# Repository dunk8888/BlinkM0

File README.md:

# BlinkM0

This is research for a potential new BlinkM, based on ATSAMD21.

It builds on research in previous repos like:

- blinkm_mk2
- samd11toy
- blinkm
- blink1

Some of the proposed features:
- Tiny form, for small embedded uses
- Trinket M0 compatible
- CircuitPython capable
- USB MSD programmable (MSD bootlaoder)
- At least 2 inputs
- logic level-shifters for LEDs

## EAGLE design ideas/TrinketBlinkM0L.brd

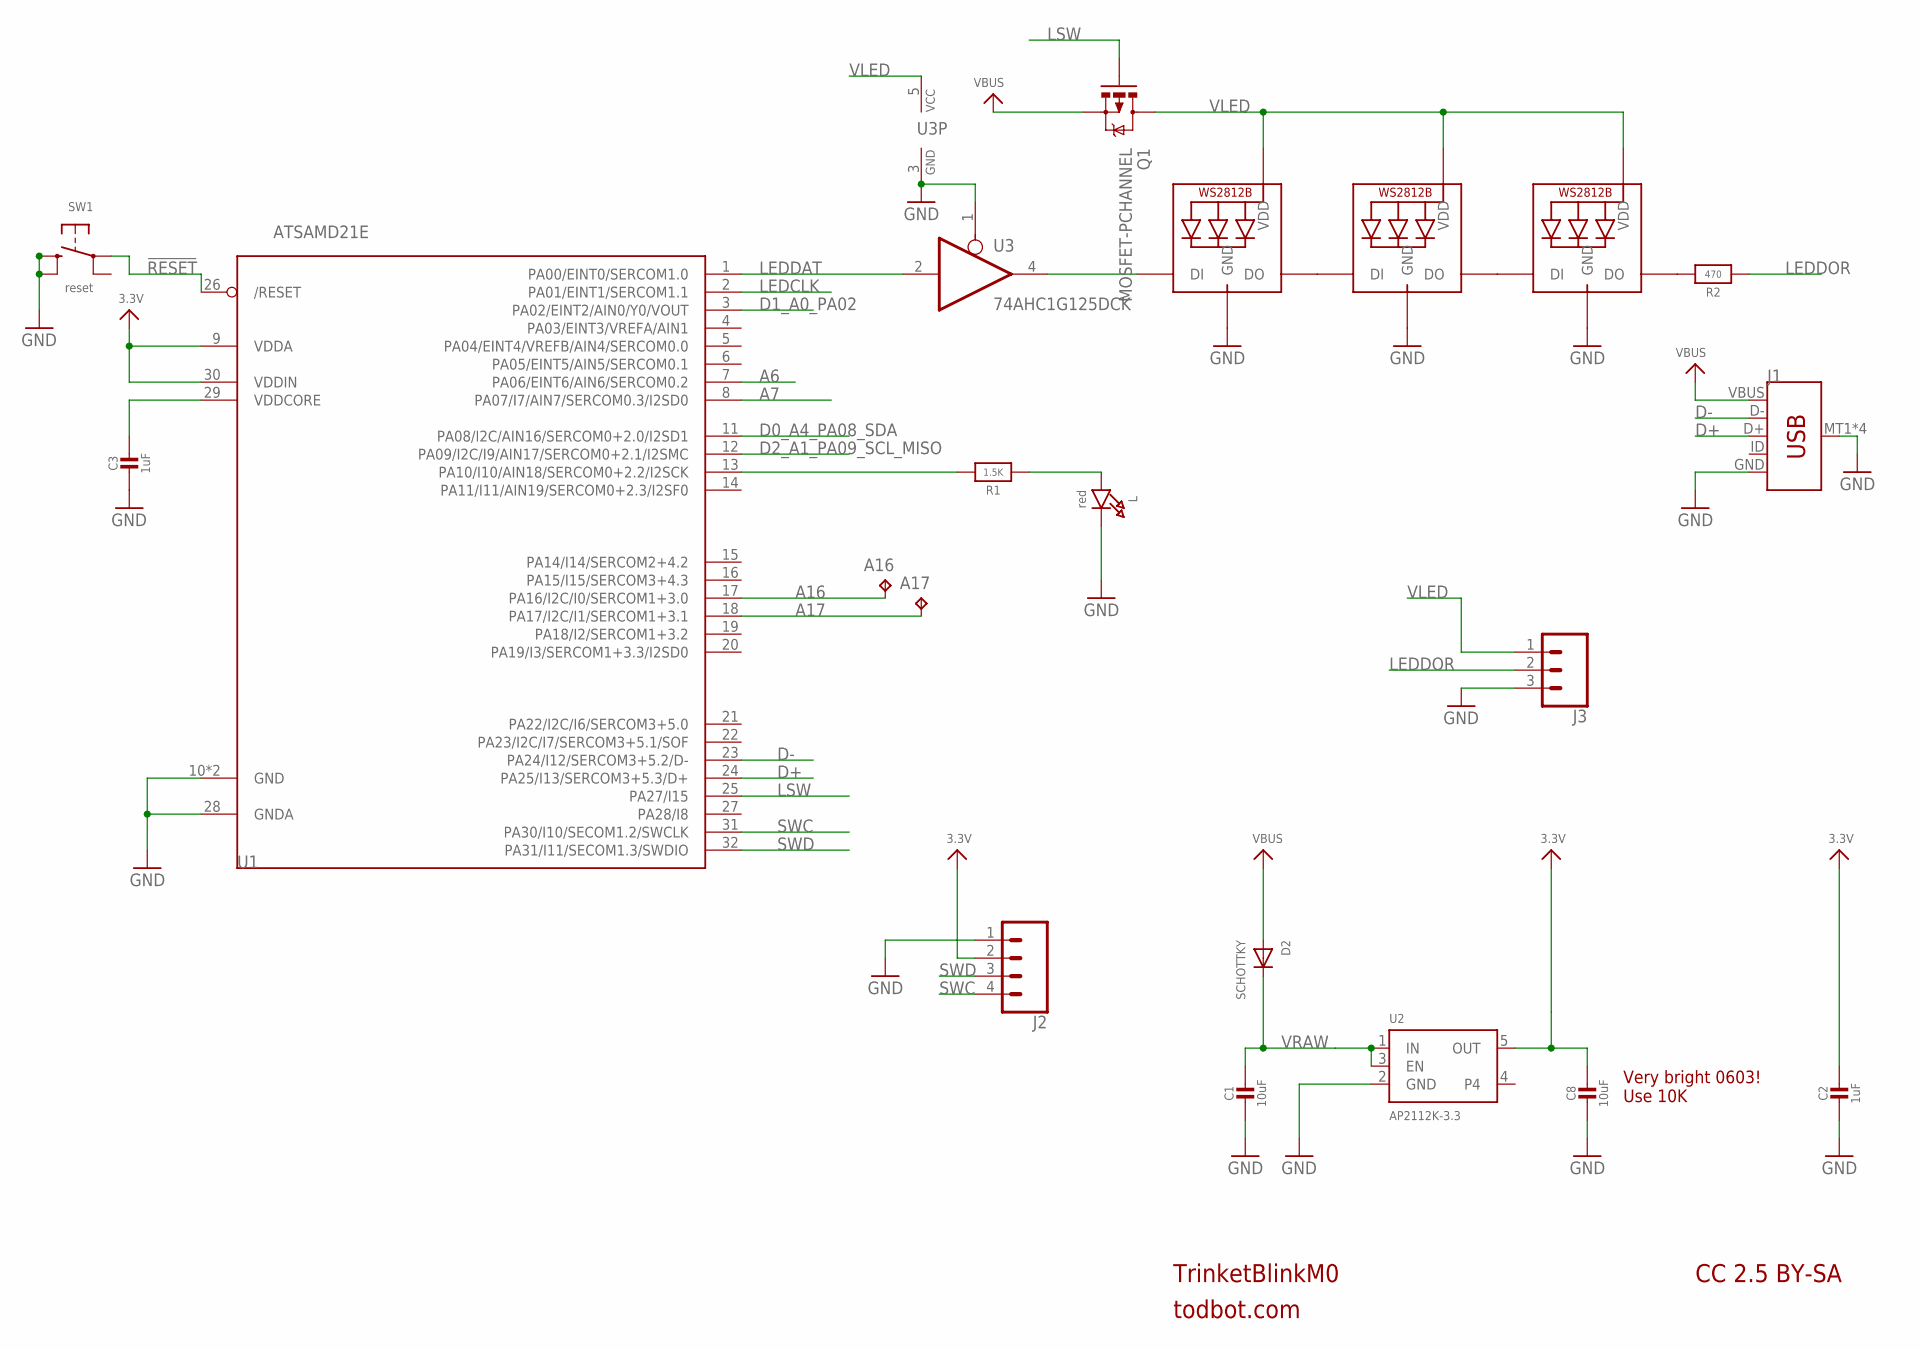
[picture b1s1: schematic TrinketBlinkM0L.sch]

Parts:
A16, A17: TPB1,27; B1,27
C1, C8: 10uF; 0805-NO
C2, C3: 1uF; 0603-NO
D2: SCHOTTKY; SOD-123FL
J1: USB_MICRO-B_SMT; USB-MICROB
J2: CONN_04; 1X04
J3: CONN_03; 1X03
L: red; CHIPLED_0603_NOOUTLINE
LED1, LED2, LED3: WS2812B3535; LED3535
Q1: MOSFET-PCHANNEL; SOT23-3
R1: 1.5K; 0603-NO
R2: 470; 0603-NO
SW1: reset; BTN_KMR2_4.6X2.8
U1: ATSAMD21E; QFN32_5MM
U2: AP2112K-3.3; SOT23-5
U3: 74AHC1G125DCK; SC70-5

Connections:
3.3V: C2.1, C8.1, J2.2, U1.9 (VDDA), U1.30 (VDDIN), U2.5 (OUT)
!RESET: SW1.A, U1.26 (/RESET)
A6: U1.7 (PA06/EINT6/AIN6/SERCOM0.2)
A7: U1.8 (PA07/I7/AIN7/SERCOM0.3/I2SD0)
A16: A16.TP, U1.17 (PA16/I2C/I0/SERCOM1+3.0)
A17: A17.TP, U1.18 (PA17/I2C/I1/SERCOM1+3.1)
D0_A4_PA08_SDA: U1.11 (PA08/I2C/AIN16/SERCOM0+2.0/I2SD1)
D1_A0_PA02: U1.3 (PA02/EINT2/AIN0/Y0/VOUT)
D2_A1_PA09_SCL_MISO: U1.12 (PA09/I2C/I9/AIN17/SERCOM0+2.1/I2SMC)
D+: J1.D+, U1.24 (PA25/I13/SERCOM3+5.3/D+)
D-: J1.D-, U1.23 (PA24/I12/SERCOM3+5.2/D-)
GND: C1.2, C2.2, C3.2, C8.2, J1.GND, J1.MT1 (SHIELD), J1.MT2 (SHIELD), J1.P$1 (SHIELD), J1.P$2 (SHIELD), J2.1, J3.3, L.C, LED1.4 (GND), LED2.4 (GND), LED3.4 (GND), SW1.B (S), SW1.B' (S1), U1.10 (GND), U1.28 (GNDA), U1.33 (GND), U2.2 (GND), U3.1 (OE), U3.3 (GND)
LEDCLK: U1.2 (PA01/EINT1/SERCOM1.1)
LEDDAT: U1.1 (PA00/EINT0/SERCOM1.0), U3.2 (I)
LEDDATO: LED1.1 (DI), U3.4 (O)
LEDDOR: J3.2, R2.1
LSW: Q1.1 (G), U1.25 (PA27/I15)
unnamed: L.A, R1.1
unnamed: R1.2, U1.13 (PA10/I10/AIN18/SERCOM0+2.2/I2SCK)
unnamed: LED1.3 (DO), LED2.1 (DI)
unnamed: LED2.3 (DO), LED3.1 (DI)
unnamed: LED3.3 (DO), R2.2
SWC: J2.4, U1.31 (PA30/I10/SECOM1.2/SWCLK)
SWD: J2.3, U1.32 (PA31/I11/SECOM1.3/SWDIO)
VBUS: D2.A, J1.VBUS, Q1.2 (S)
VDDCORE: C3.1, U1.29 (VDDCORE)
VLED: J3.1, LED1.2 (VDD), LED2.2 (VDD), LED3.2 (VDD), Q1.3 (D), U3.5 (VCC)
VRAW: C1.1, D2.C, U2.1 (IN), U2.3 (EN)

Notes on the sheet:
TrinketBlinkM0
todbot.com
CC 2.5 BY-SA
Very bright 0603! Use 10K

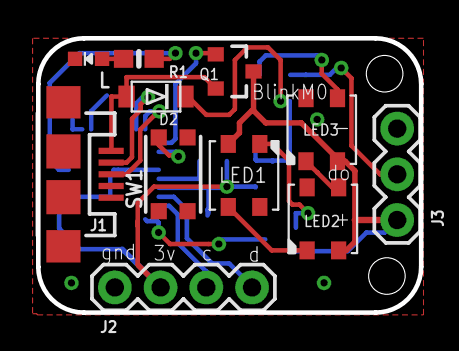
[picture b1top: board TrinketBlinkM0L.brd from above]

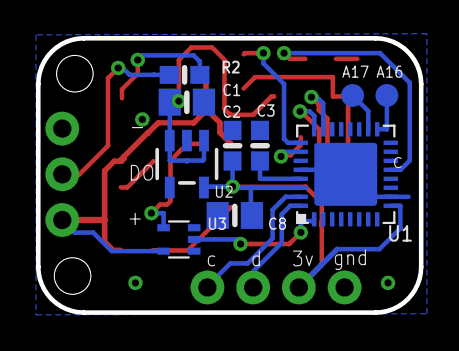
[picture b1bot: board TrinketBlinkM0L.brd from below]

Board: 2 copper layers, 21.3 x 15.2 mm, 21 parts (10 on the bottom side), 22 nets.

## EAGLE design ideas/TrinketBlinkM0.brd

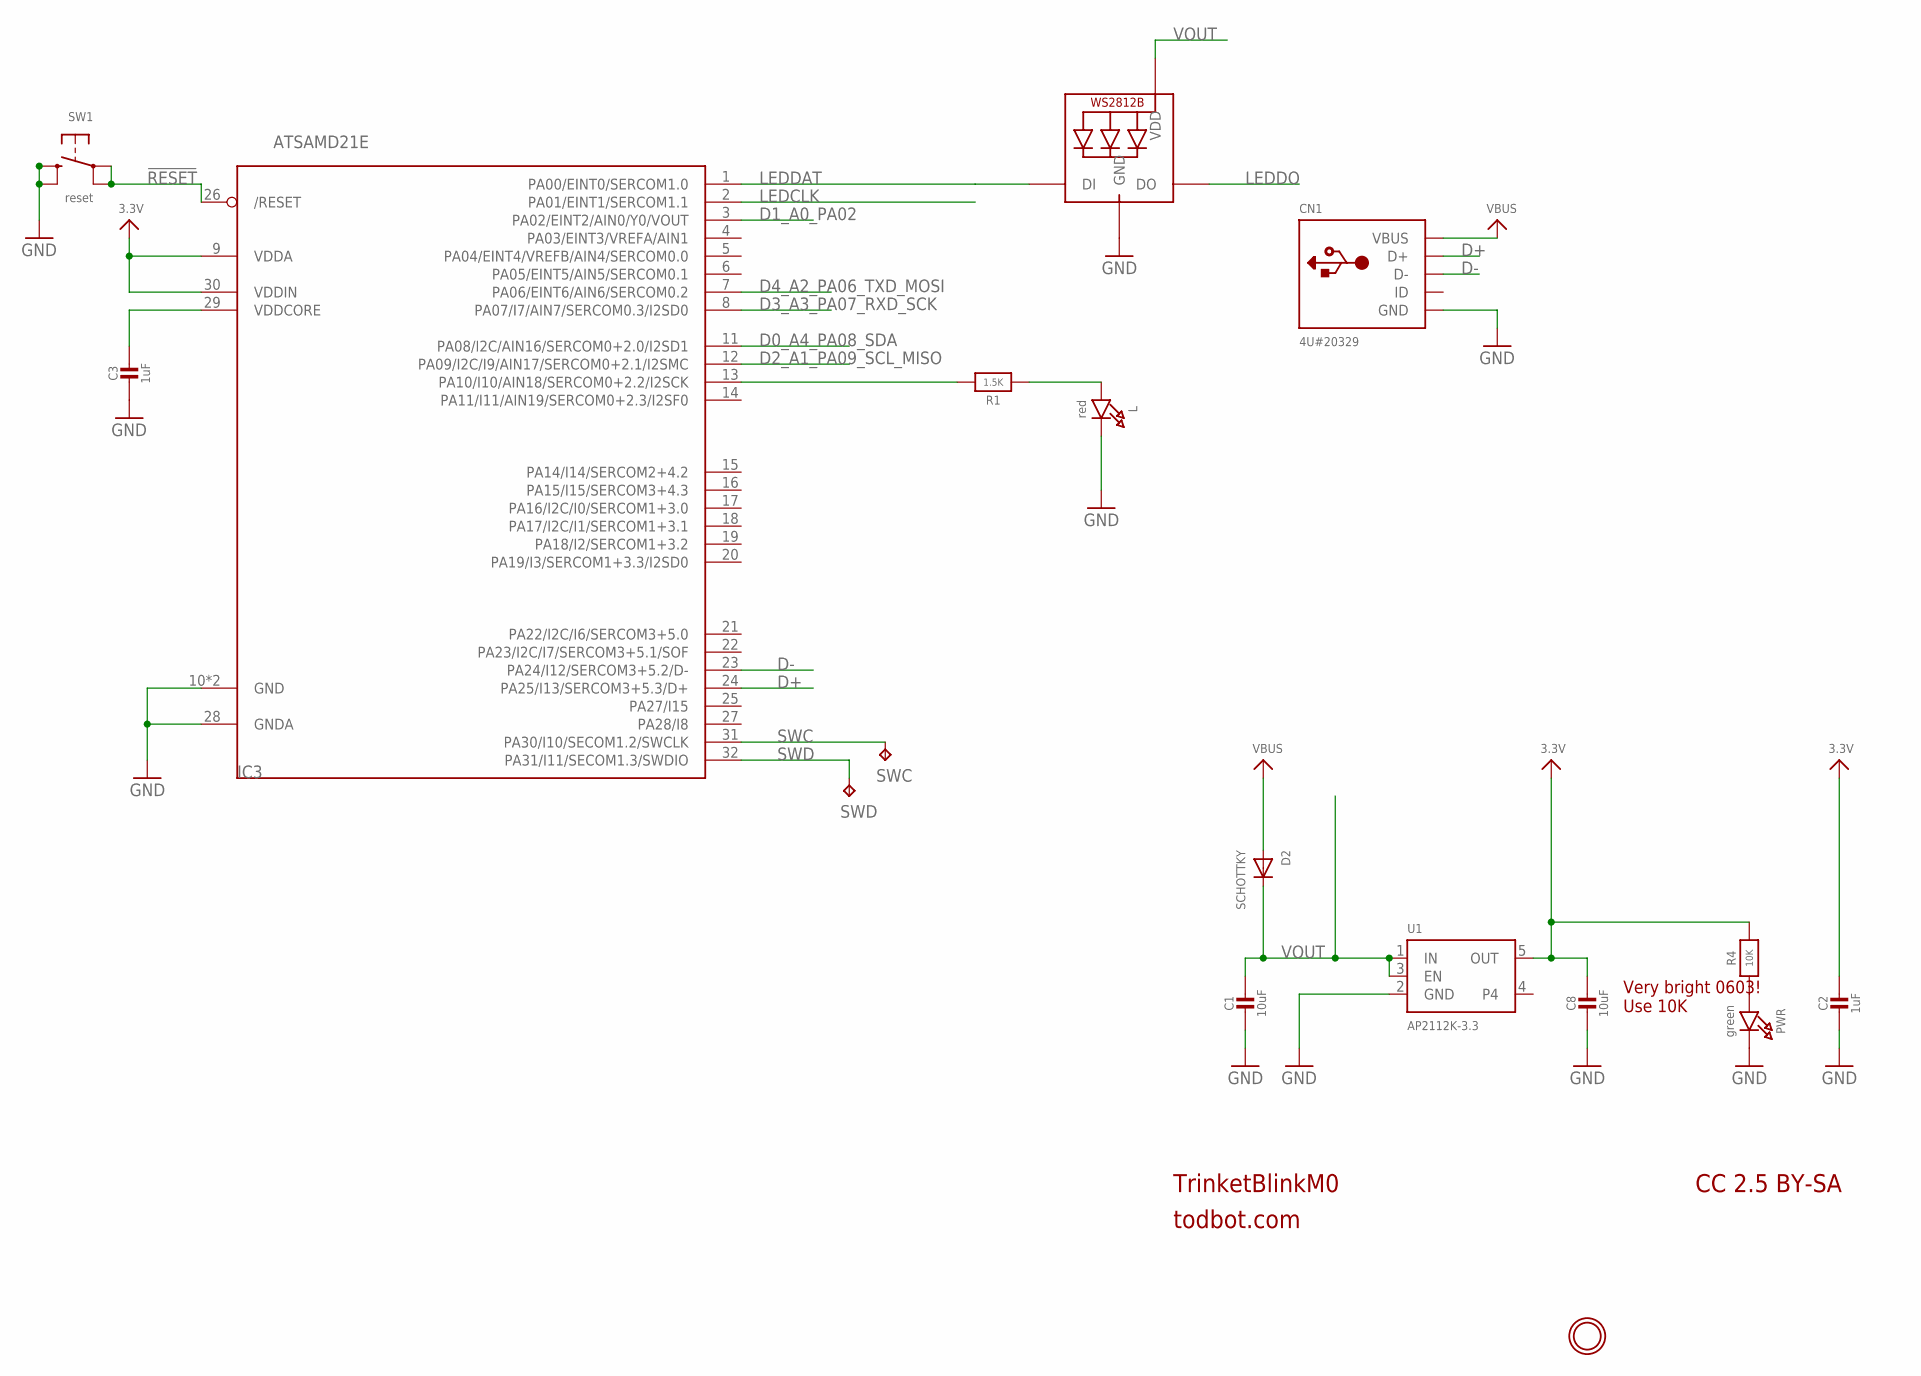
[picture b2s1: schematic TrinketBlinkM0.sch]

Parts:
C1, C8: 10uF; 0805-NO
C2, C3: 1uF; 0603-NO
CN1: 4U#20329; 4UCONN_20329_V2
D2: SCHOTTKY; SOD-123FL
IC3: ATSAMD21E; QFN32_5MM
L: red; CHIPLED_0603_NOOUTLINE
LED1: WS2812B5050; WS2812B
PWR: green; CHIPLED_0603_NOOUTLINE
R1: 1.5K; 0603-NO
R4: 10K; 0603-NO
SW1: reset; BTN_KMR2_4.6X2.8
SWC: TPB1,27; B1,27
SWD: TPB1,27; B1,27
U1: AP2112K-3.3; SOT23-5
U$8: MOUNTINGHOLE2.0; MOUNTINGHOLE_2.0_PLATED

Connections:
3.3V: C2.1, C8.1, IC3.9 (VDDA), IC3.30 (VDDIN), R4.2, U1.5 (OUT)
!RESET: IC3.26 (/RESET), SW1.A, SW1.A' (P1)
D0_A4_PA08_SDA: IC3.11 (PA08/I2C/AIN16/SERCOM0+2.0/I2SD1)
D1_A0_PA02: IC3.3 (PA02/EINT2/AIN0/Y0/VOUT)
D2_A1_PA09_SCL_MISO: IC3.12 (PA09/I2C/I9/AIN17/SERCOM0+2.1/I2SMC)
D3_A3_PA07_RXD_SCK: IC3.8 (PA07/I7/AIN7/SERCOM0.3/I2SD0)
D4_A2_PA06_TXD_MOSI: IC3.7 (PA06/EINT6/AIN6/SERCOM0.2)
D+: CN1.D+, IC3.24 (PA25/I13/SERCOM3+5.3/D+)
D-: CN1.D-, IC3.23 (PA24/I12/SERCOM3+5.2/D-)
GND: C1.2, C2.2, C3.2, C8.2, CN1.BASE@1 (GND), CN1.BASE@2 (GND), CN1.GND, CN1.SPRT@1 (GND), CN1.SPRT@2 (GND), CN1.SPRT@3 (GND), CN1.SPRT@4 (GND), IC3.10 (GND), IC3.28 (GNDA), IC3.33 (GND), L.C, LED1.3-GND (GND), PWR.C, SW1.B (S), SW1.B' (S1), U1.2 (GND)
LEDCLK: IC3.2 (PA01/EINT1/SERCOM1.1)
LEDDAT: IC3.1 (PA00/EINT0/SERCOM1.0), LED1.4-DIN (DI)
LEDDO: LED1.2-DOUT (DO)
unnamed: L.A, R1.1
unnamed: IC3.13 (PA10/I10/AIN18/SERCOM0+2.2/I2SCK), R1.2
unnamed: PWR.A, R4.1
SWC: IC3.31 (PA30/I10/SECOM1.2/SWCLK), SWC.TP
SWD: IC3.32 (PA31/I11/SECOM1.3/SWDIO), SWD.TP
VBUS: CN1.VBUS, D2.A
VDDCORE: C3.1, IC3.29 (VDDCORE)
VOUT: C1.1, D2.C, LED1.1-VDD (VDD), U1.1 (IN), U1.3 (EN)

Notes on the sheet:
TrinketBlinkM0
todbot.com
CC 2.5 BY-SA
Very bright 0603! Use 10K

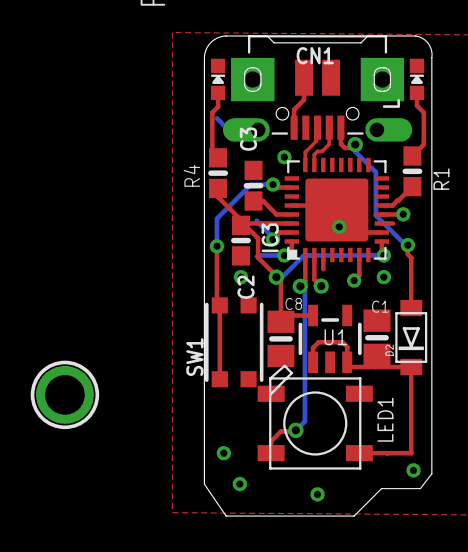
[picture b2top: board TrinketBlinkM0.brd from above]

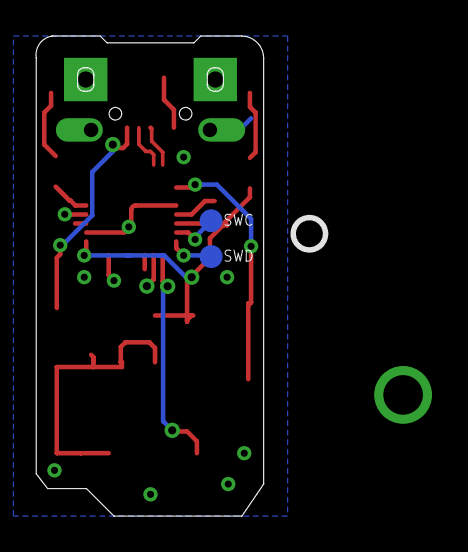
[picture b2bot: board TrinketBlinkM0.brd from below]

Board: 2 copper layers, 12.6 x 26.7 mm, 20 parts (4 on the bottom side), 14 nets.

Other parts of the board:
U$1: TRINKET_M0_BOTTOM
U$12: PCBFEAT-REV-040
U$20: TRINKET_M0_TOP

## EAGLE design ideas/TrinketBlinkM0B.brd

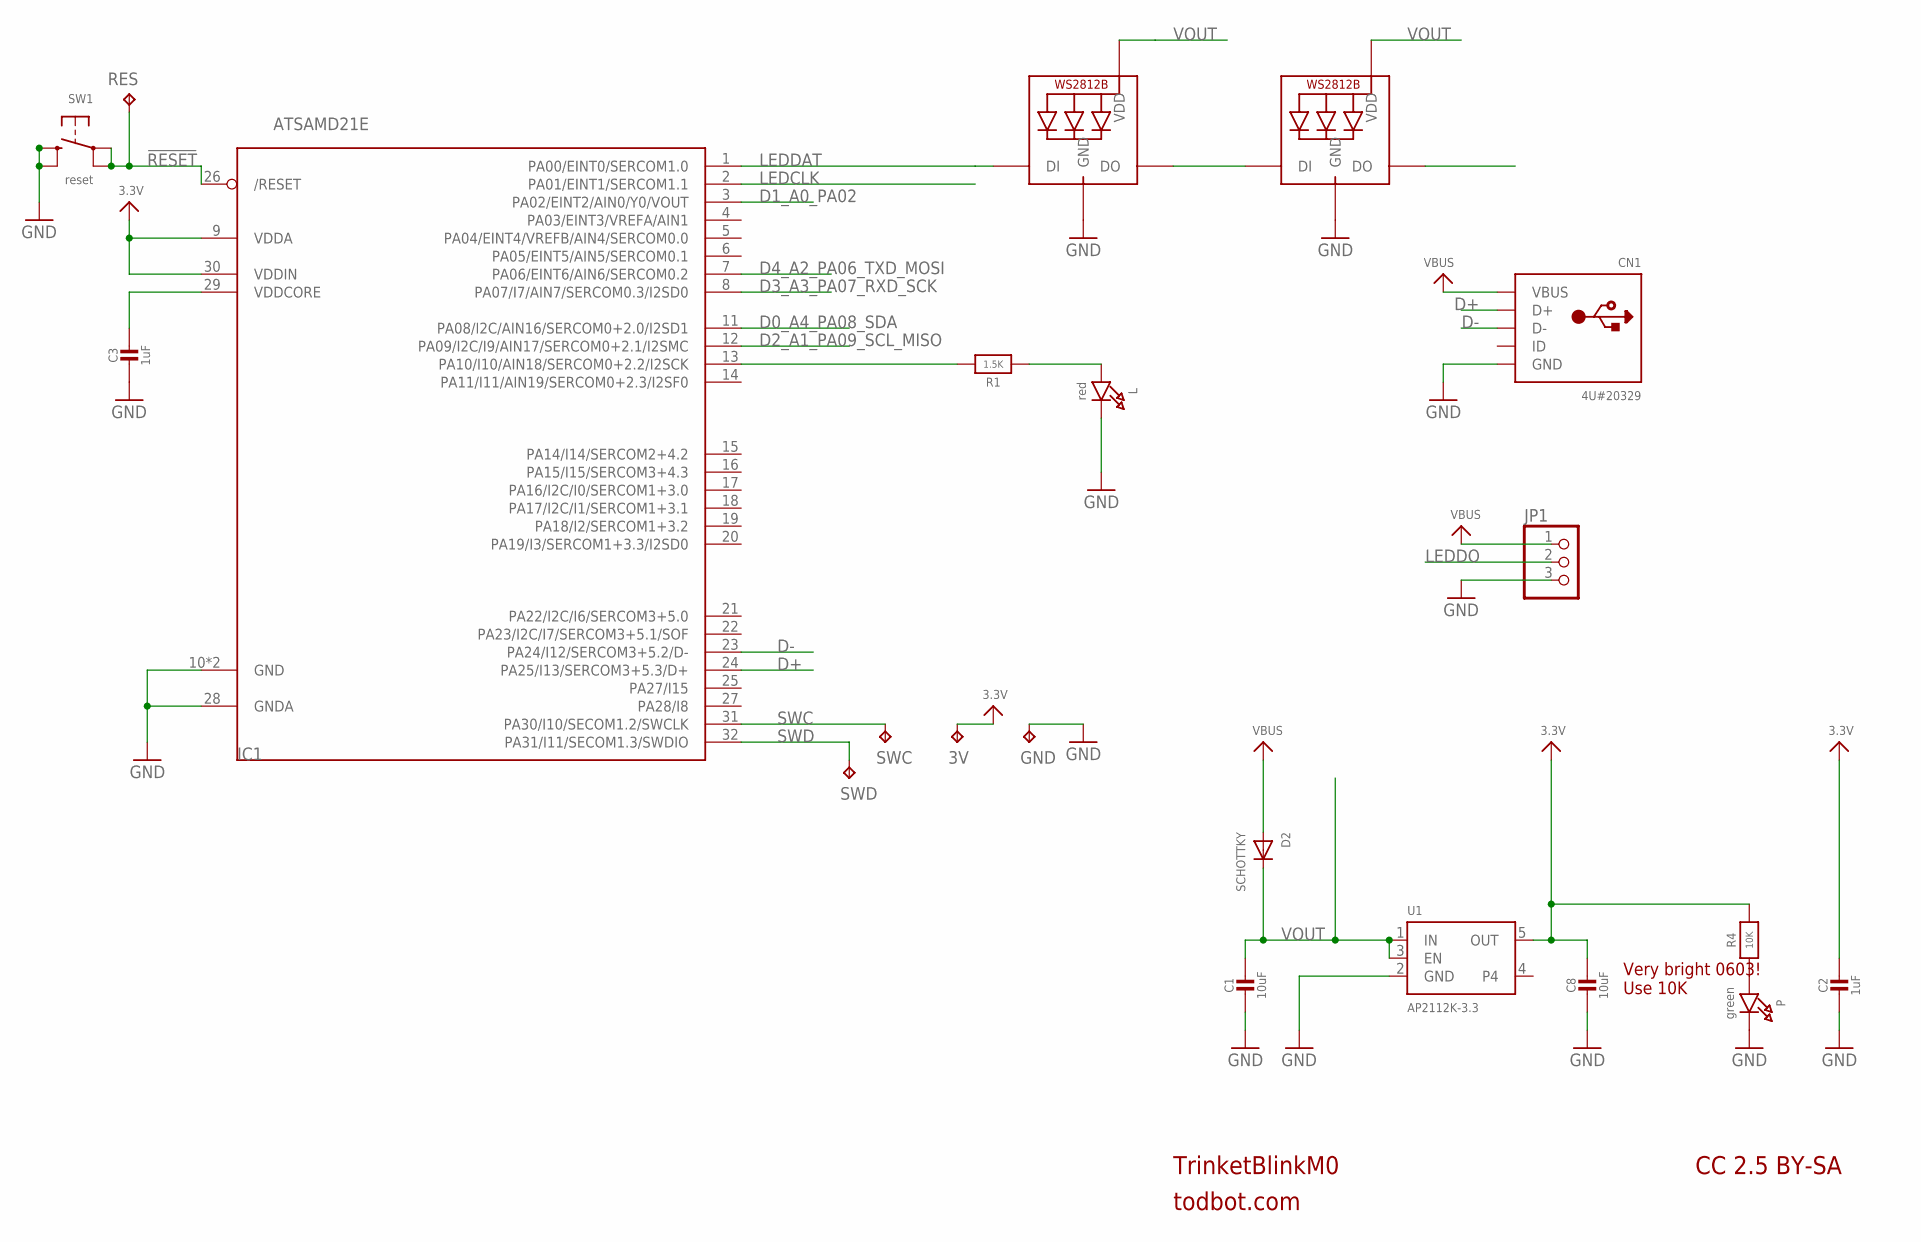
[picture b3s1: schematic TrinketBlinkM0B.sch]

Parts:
3V: TPB1,27; B1,27
C1, C8: 10uF; 0805-NO
C2, C3: 1uF; 0603-NO
CN1: 4U#20329; 4UCONN_20329_V2
D2: SCHOTTKY; SOD-123FL
GND: TPB1,27; B1,27
IC1: ATSAMD21E; QFN32_5MM
JP1: PINHD-1X3CB; 1X03-CLEANBIG
L: red; CHIPLED_0603_NOOUTLINE
LED1, LED2: WS2812B_5050N; WS2812B-NARROW
P: green; CHIPLED_0603_NOOUTLINE
R1: 1.5K; 0603-NO
R4: 10K; 0603-NO
RES: TPB1,27; B1,27
SW1: reset; BTN_KMR2_4.6X2.8
SWC: TPB1,27; B1,27
SWD: TPB1,27; B1,27
U1: AP2112K-3.3; SOT23-5

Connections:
3.3V: 3V.TP, C2.1, C8.1, IC1.9 (VDDA), IC1.30 (VDDIN), R4.2, U1.5 (OUT)
!RESET: IC1.26 (/RESET), RES.TP, SW1.A, SW1.A' (P1)
D0_A4_PA08_SDA: IC1.11 (PA08/I2C/AIN16/SERCOM0+2.0/I2SD1)
D1_A0_PA02: IC1.3 (PA02/EINT2/AIN0/Y0/VOUT)
D2_A1_PA09_SCL_MISO: IC1.12 (PA09/I2C/I9/AIN17/SERCOM0+2.1/I2SMC)
D3_A3_PA07_RXD_SCK: IC1.8 (PA07/I7/AIN7/SERCOM0.3/I2SD0)
D4_A2_PA06_TXD_MOSI: IC1.7 (PA06/EINT6/AIN6/SERCOM0.2)
D+: CN1.D+, IC1.24 (PA25/I13/SERCOM3+5.3/D+)
D-: CN1.D-, IC1.23 (PA24/I12/SERCOM3+5.2/D-)
GND: C1.2, C2.2, C3.2, C8.2, CN1.BASE@1 (GND), CN1.BASE@2 (GND), CN1.GND, CN1.SPRT@1 (GND), CN1.SPRT@2 (GND), CN1.SPRT@3 (GND), CN1.SPRT@4 (GND), GND.TP, IC1.10 (GND), IC1.28 (GNDA), IC1.33 (GND), JP1.3, L.C, LED1.3-GND (GND), LED2.3-GND (GND), P.C, SW1.B (S), SW1.B' (S1), U1.2 (GND)
LEDCLK: IC1.2 (PA01/EINT1/SERCOM1.1)
LEDDAT: IC1.1 (PA00/EINT0/SERCOM1.0), LED1.4-DIN (DI)
LEDDO: JP1.2, LED2.2-DOUT (DO)
unnamed: L.A, R1.1
unnamed: IC1.13 (PA10/I10/AIN18/SERCOM0+2.2/I2SCK), R1.2
unnamed: LED1.2-DOUT (DO), LED2.4-DIN (DI)
unnamed: P.A, R4.1
SWC: IC1.31 (PA30/I10/SECOM1.2/SWCLK), SWC.TP
SWD: IC1.32 (PA31/I11/SECOM1.3/SWDIO), SWD.TP
VBUS: CN1.VBUS, D2.A, JP1.1
VDDCORE: C3.1, IC1.29 (VDDCORE)
VOUT: C1.1, D2.C, LED1.1-VDD (VDD), LED2.1-VDD (VDD), U1.1 (IN), U1.3 (EN)

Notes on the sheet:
TrinketBlinkM0
todbot.com
CC 2.5 BY-SA
Very bright 0603! Use 10K

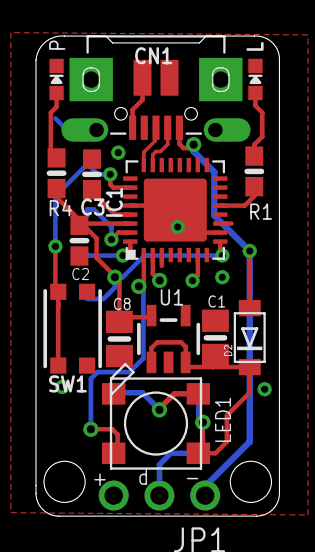
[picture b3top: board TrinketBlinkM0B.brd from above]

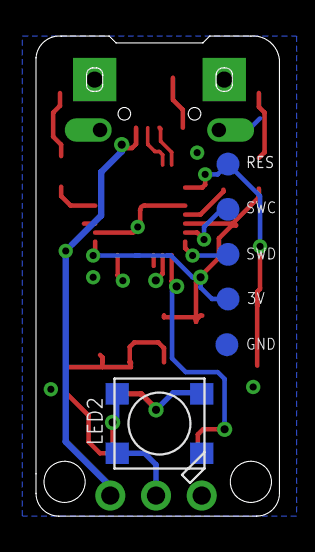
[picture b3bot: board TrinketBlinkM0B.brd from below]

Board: 2 copper layers, 13.5 x 26.7 mm, 23 parts (7 on the bottom side), 16 nets.

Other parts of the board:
U$1: TRINKET_M0_BOTTOM
U$20: TRINKET_M0_TOP

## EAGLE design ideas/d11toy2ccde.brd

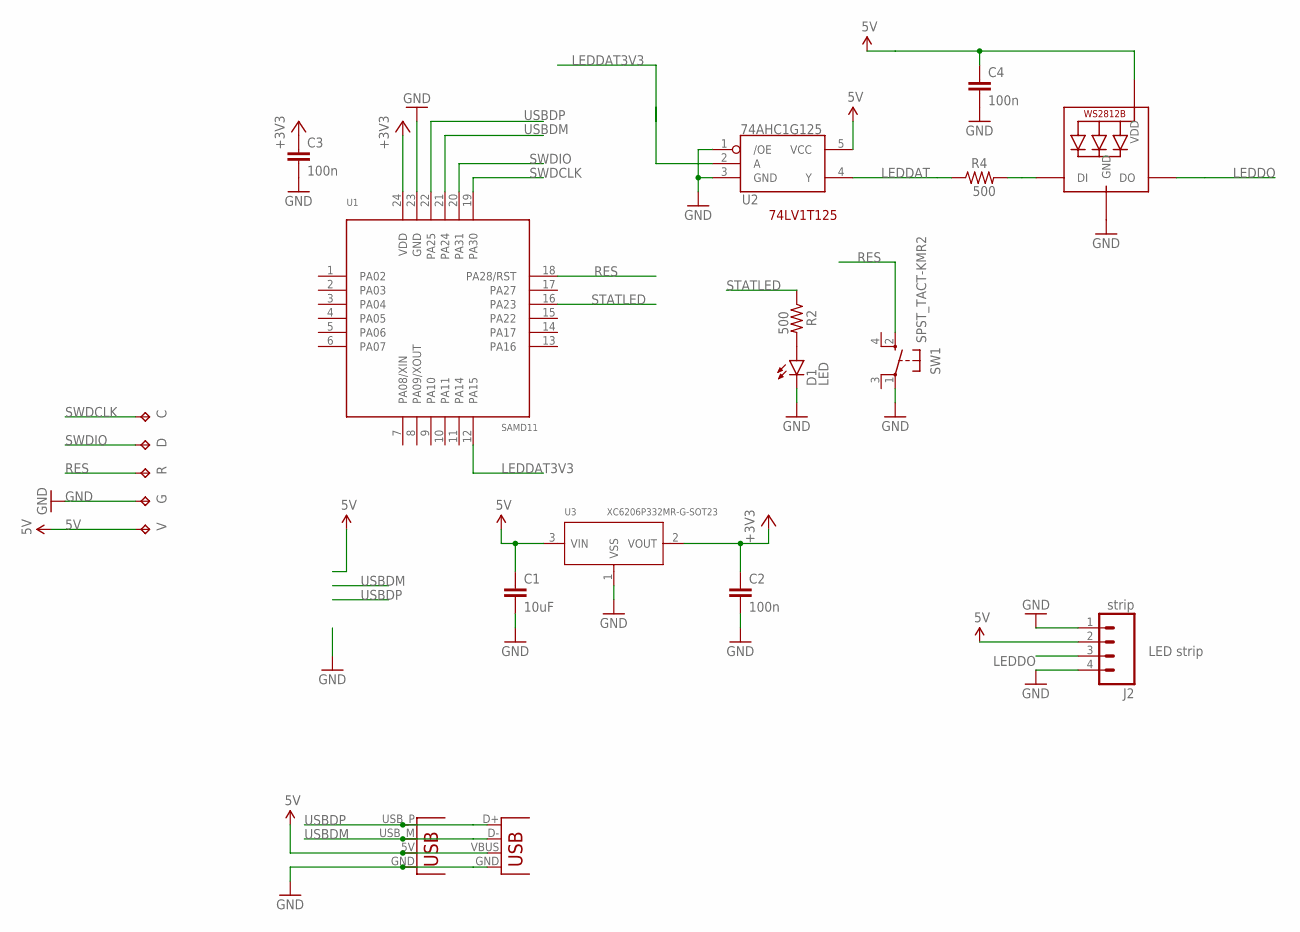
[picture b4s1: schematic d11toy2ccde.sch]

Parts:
C: TPTP08R; TP08R
C1: 10uF; 0603-CAP
C2, C3, C4: 100n; 0603-CAP
D: TPTP08R; TP08R
D1: LED; LED-0603
G: TPTP08R; TP08R
J2: strip; 1X04_NO_SILK_ALL_ROUND
JP1: USBPCB; USB-A-PCB
JP3: USB-MICROB
LED1: WS2812B5050; WS2812B
R: TPTP08R; TP08R
R2, R4: 500; 0603-RES
SW1: SPST_TACT-KMR2; KMR2
U1: SAMD11; QFN24
U2: 74AHC1G125; SOT23-5
U3: XC6206P332MR-G-SOT23; SOT-23
V: TPTP08R; TP08R

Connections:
5V: C1.1, C4.1, J2.2, JP1.5V (VBUS), JP3.VBUS, LED1.1-VDD (VDD), U2.5 (VCC), U3.3 (VIN), V.TP
+3V3: C2.1, C3.1, U1.24 (VDD), U3.2 (VOUT)
GND: C1.2, C2.2, C3.2, C4.2, D1.C, G.TP, J2.1, J2.4, JP1.GND, JP3.GND, LED1.3-GND (GND), SW1.1, U1.23 (GND), U2.1 (/OE), U2.3 (GND), U3.1 (VSS)
LEDDAT: R4.1, U2.4 (Y)
LEDDAT3V3: U1.12 (PA15), U2.2 (A)
LEDDO: J2.3, LED1.2-DOUT (DO)
unnamed: D1.A, R2.2
unnamed: LED1.4-DIN (DI), R4.2
RES: R.TP, SW1.2 (S), U1.18 (PA28/RST)
STATLED: R2.1, U1.16 (PA23)
SWDCLK: C.TP, U1.19 (PA30)
SWDIO: D.TP, U1.20 (PA31)
USBDM: JP1.USB_M (D-), JP3.D-, U1.21 (PA24)
USBDP: JP1.USB_P (D+), JP3.D+, U1.22 (PA25)

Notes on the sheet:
LED strip
74LV1T125

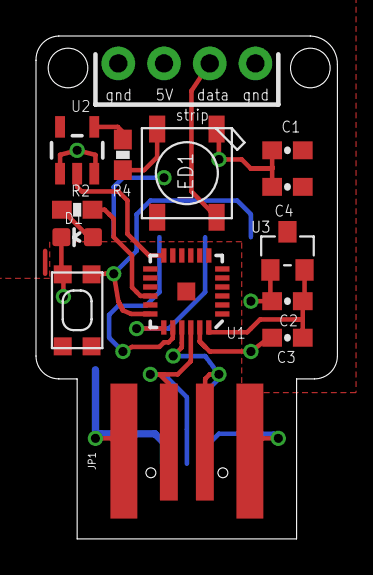
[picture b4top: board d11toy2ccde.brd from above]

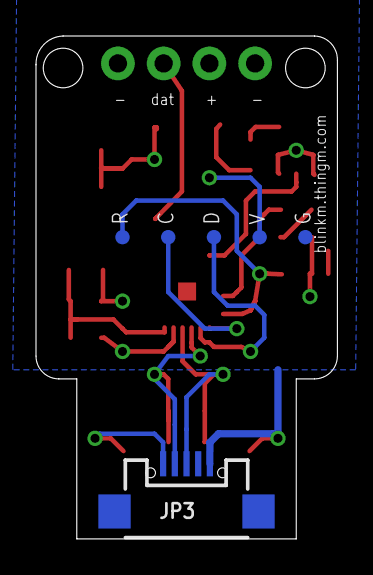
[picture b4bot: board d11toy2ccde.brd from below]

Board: 2 copper layers, 16.7 x 27.9 mm, 20 parts (6 on the bottom side), 14 nets.

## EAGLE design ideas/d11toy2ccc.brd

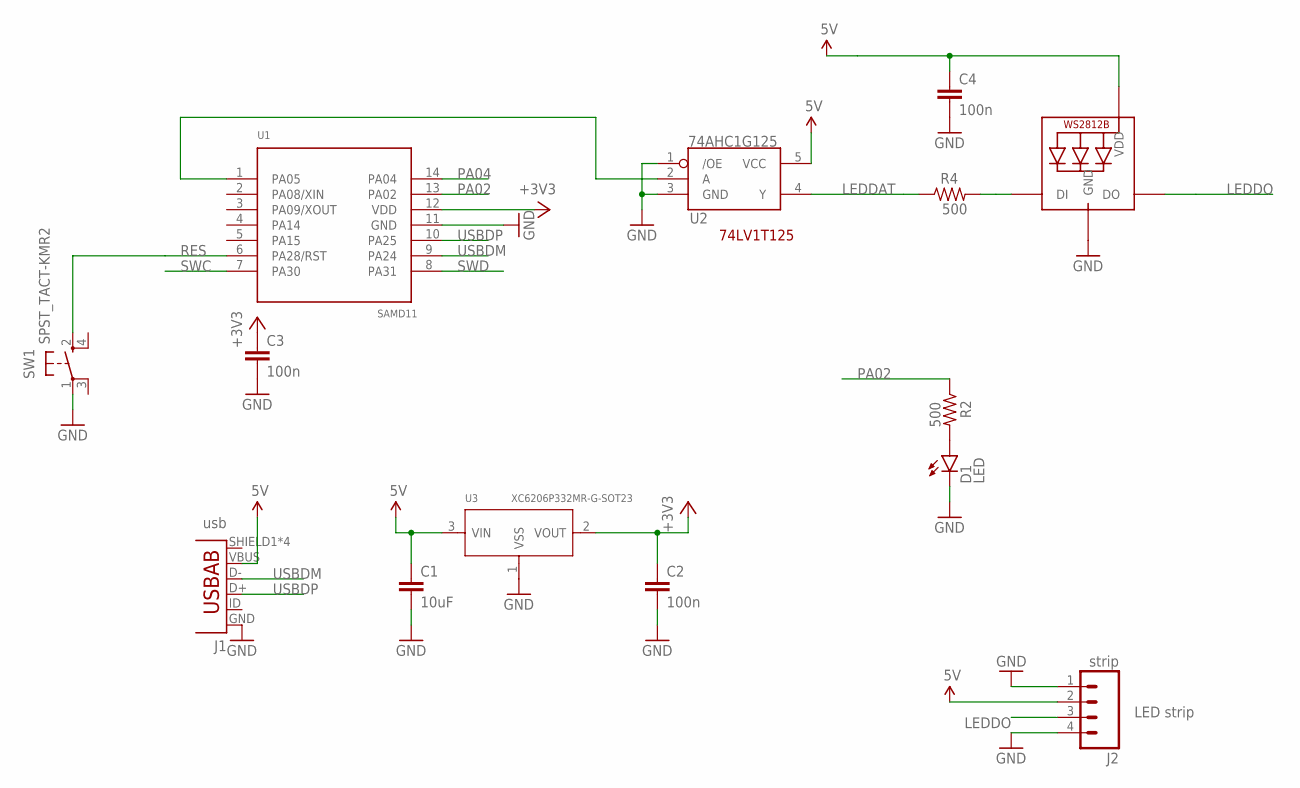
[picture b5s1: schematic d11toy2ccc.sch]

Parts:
C1: 10uF; 0603-CAP
C2, C3, C4: 100n; 0603-CAP
D1: LED; LED-0603
J1: usb; USB-AB-MICRO-SMD
J2: strip; 1X04_NO_SILK_ALL_ROUND
LED1: WS2812B5050; WS2812B
R2, R4: 500; 0603-RES
SW1: SPST_TACT-KMR2; KMR2
U1: SAMD11; SO14
U2: 74AHC1G125; SOT23-5
U3: XC6206P332MR-G-SOT23; SOT-23

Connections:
5V: C1.1, C4.1, J1.VBUS, J2.2, LED1.1-VDD (VDD), U2.5 (VCC), U3.3 (VIN)
+3V3: C2.1, C3.1, U1.12 (VDD), U3.2 (VOUT)
GND: C1.2, C2.2, C3.2, C4.2, D1.C, J1.GND, J2.1, J2.4, LED1.3-GND (GND), SW1.1, U1.11 (GND), U2.1 (/OE), U2.3 (GND), U3.1 (VSS)
LEDDAT: R4.1, U2.4 (Y)
LEDDAT3V3: U1.1 (PA05), U2.2 (A)
LEDDO: J2.3, LED1.2-DOUT (DO)
unnamed: D1.A, R2.2
unnamed: LED1.4-DIN (DI), R4.2
PA02: R2.1, U1.13 (PA02)
PA04: U1.14 (PA04)
RES: SW1.2 (S), U1.6 (PA28/RST)
SWC: U1.7 (PA30)
SWD: U1.8 (PA31)
USBDM: J1.D-, U1.9 (PA24)
USBDP: J1.D+, U1.10 (PA25)

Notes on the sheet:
LED strip
74LV1T125

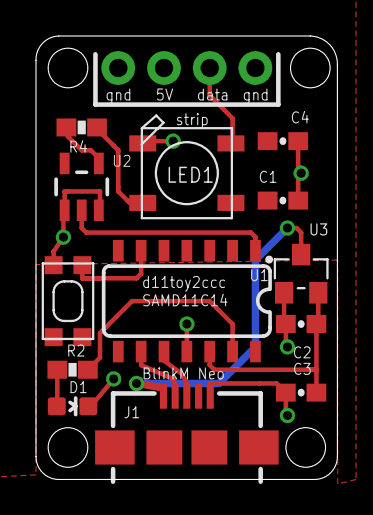
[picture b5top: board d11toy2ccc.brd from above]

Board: 2 copper layers, 16.7 x 24.6 mm, 14 parts (0 on the bottom side), 12 nets.

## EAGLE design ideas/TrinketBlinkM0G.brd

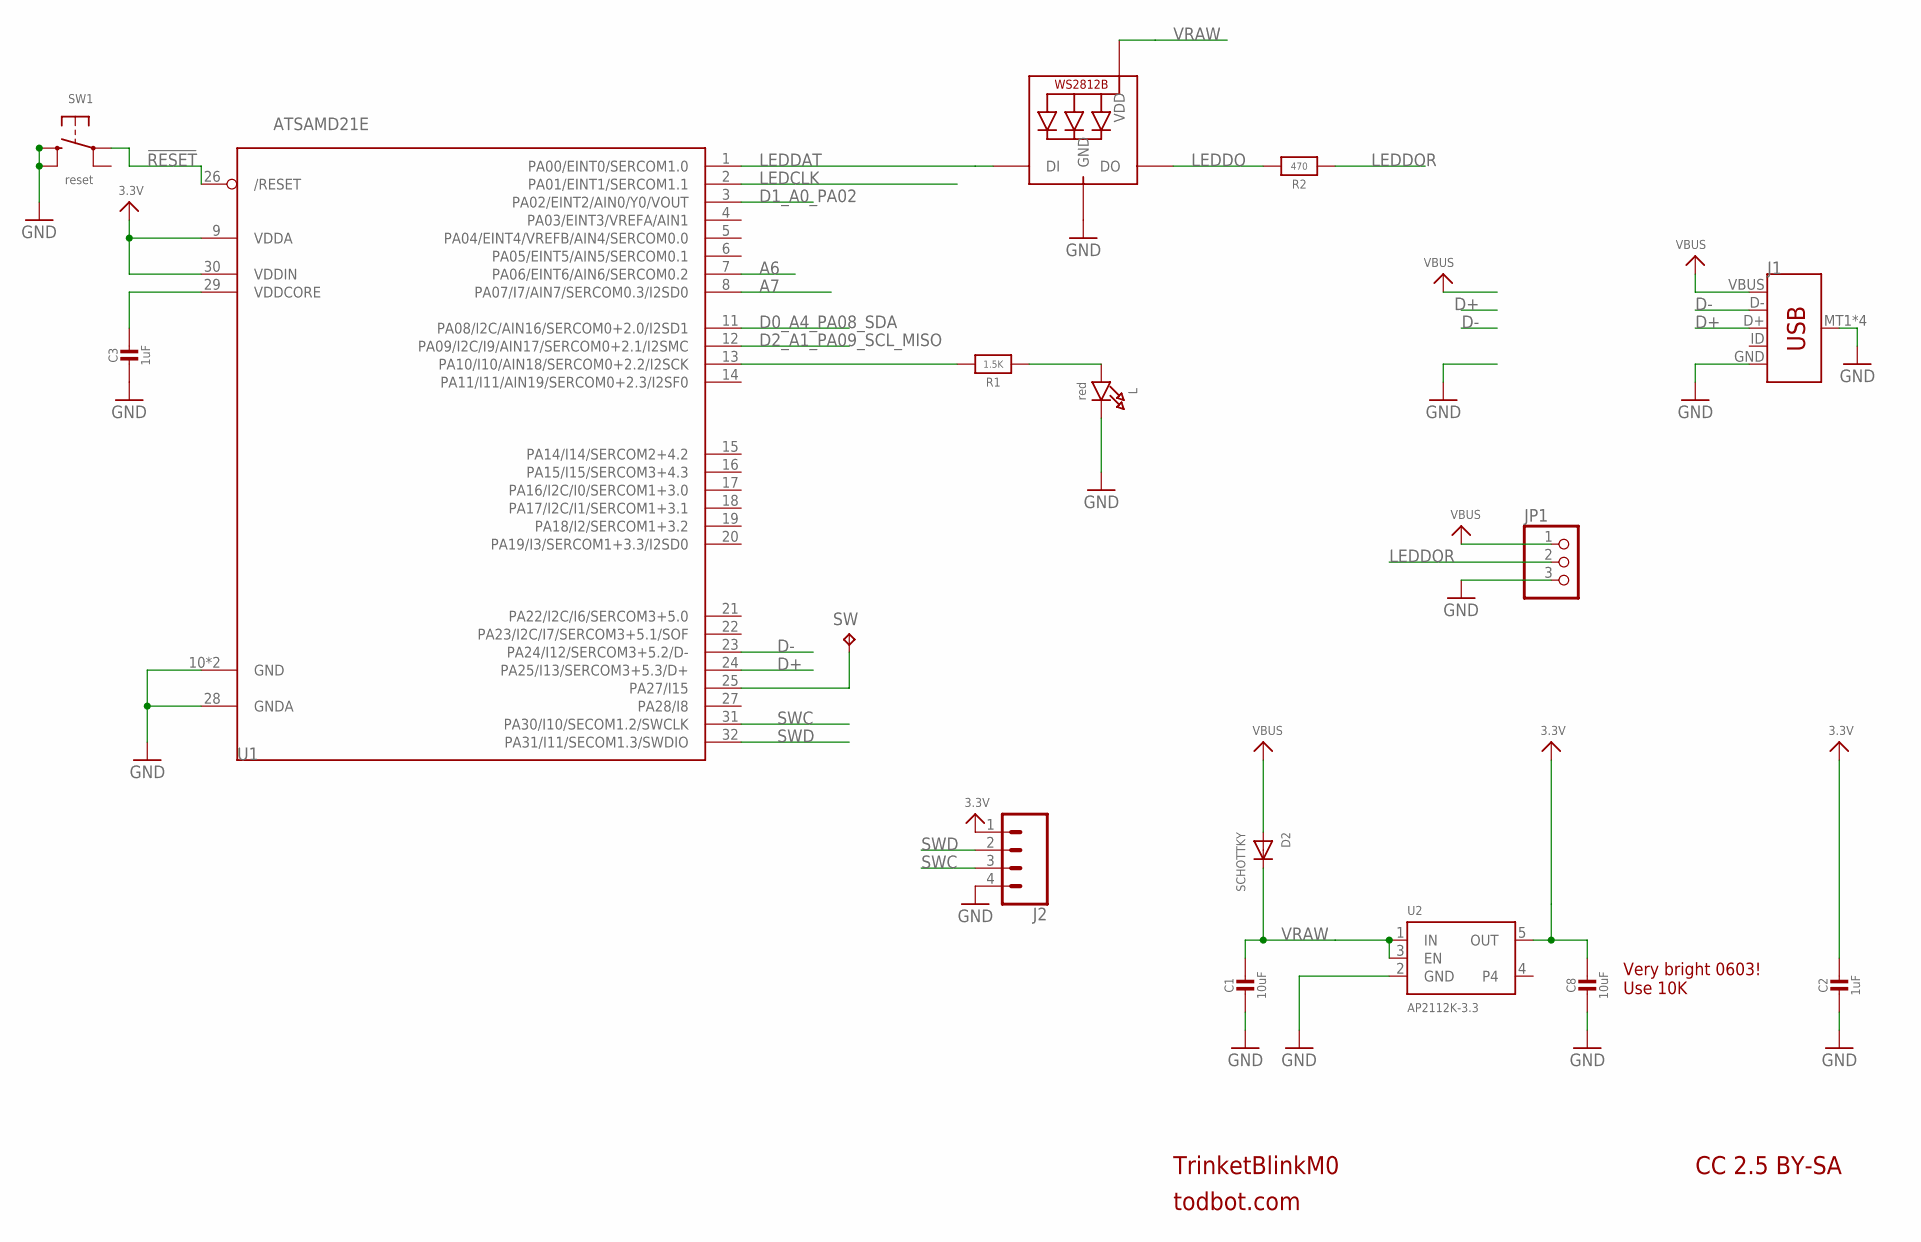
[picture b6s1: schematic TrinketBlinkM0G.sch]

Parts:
C1, C8: 10uF; 0805-NO
C2, C3: 1uF; 0603-NO
D2: SCHOTTKY; SOD-123FL
J1: USB_MICRO-B_SMT; USB-MICROB
J2: CONN_04; 1X04
JP1: PINHD-1X3CB; 1X03-CLEANBIG
L: red; CHIPLED_0603_NOOUTLINE
LED1: WS2812B_5050N; WS2812B-NARROW
R1: 1.5K; 0603-NO
R2: 470; 0603-NO
SW: TPB1,27; B1,27
SW1: reset; BTN_KMR2_4.6X2.8
U1: ATSAMD21E; QFN32_5MM
U2: AP2112K-3.3; SOT23-5

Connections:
3.3V: C2.1, C8.1, J2.1, U1.9 (VDDA), U1.30 (VDDIN), U2.5 (OUT)
!RESET: SW1.A, U1.26 (/RESET)
A6: U1.7 (PA06/EINT6/AIN6/SERCOM0.2)
A7: U1.8 (PA07/I7/AIN7/SERCOM0.3/I2SD0)
D0_A4_PA08_SDA: U1.11 (PA08/I2C/AIN16/SERCOM0+2.0/I2SD1)
D1_A0_PA02: U1.3 (PA02/EINT2/AIN0/Y0/VOUT)
D2_A1_PA09_SCL_MISO: U1.12 (PA09/I2C/I9/AIN17/SERCOM0+2.1/I2SMC)
D+: J1.D+, U1.24 (PA25/I13/SERCOM3+5.3/D+)
D-: J1.D-, U1.23 (PA24/I12/SERCOM3+5.2/D-)
GND: C1.2, C2.2, C3.2, C8.2, J1.GND, J1.MT1 (SHIELD), J1.MT2 (SHIELD), J1.P$1 (SHIELD), J1.P$2 (SHIELD), J2.4, JP1.3, L.C, LED1.3-GND (GND), SW1.B (S), SW1.B' (S1), U1.10 (GND), U1.28 (GNDA), U1.33 (GND), U2.2 (GND)
LEDCLK: U1.2 (PA01/EINT1/SERCOM1.1)
LEDDAT: LED1.4-DIN (DI), U1.1 (PA00/EINT0/SERCOM1.0)
LEDDO: LED1.2-DOUT (DO), R2.2
LEDDOR: JP1.2, R2.1
unnamed: L.A, R1.1
unnamed: R1.2, U1.13 (PA10/I10/AIN18/SERCOM0+2.2/I2SCK)
SW: SW.TP, U1.25 (PA27/I15)
SWC: J2.3, U1.31 (PA30/I10/SECOM1.2/SWCLK)
SWD: J2.2, U1.32 (PA31/I11/SECOM1.3/SWDIO)
VBUS: D2.A, J1.VBUS, JP1.1
VDDCORE: C3.1, U1.29 (VDDCORE)
VRAW: C1.1, D2.C, LED1.1-VDD (VDD), U2.1 (IN), U2.3 (EN)

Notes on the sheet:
TrinketBlinkM0
todbot.com
CC 2.5 BY-SA
Very bright 0603! Use 10K

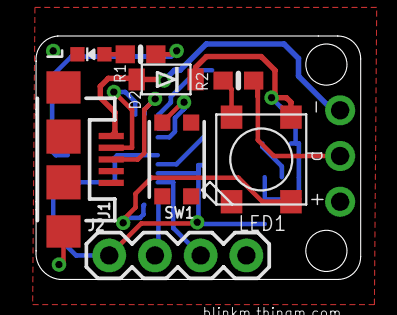
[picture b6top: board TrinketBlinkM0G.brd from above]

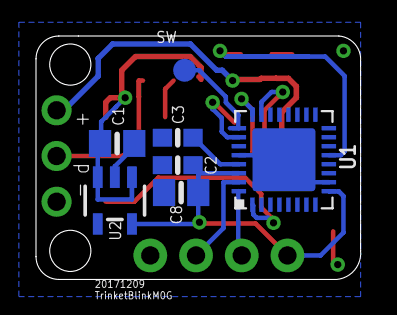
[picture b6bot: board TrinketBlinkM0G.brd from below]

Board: 2 copper layers, 18.0 x 13.5 mm, 18 parts (8 on the bottom side), 16 nets.

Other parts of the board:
U$1: TRINKET_M0_BOTTOM
U$20: TRINKET_M0_TOP

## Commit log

2017-12-12 added more ideas

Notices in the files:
parts and their libraries:
microbuilder: This work is placed in the public domain, and may be freely used for commercial and non-commercial work with the following conditions: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
SparkFun-Connectors: Licensing: Creative Commons ShareAlike 4.0 International - https://creativecommons.org/licenses/by-sa/4.0
